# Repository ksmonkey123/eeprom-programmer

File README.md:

EEPROM Programmer
=================

Arduino-based EEPROM programmer for the AT28C64B (8 KiB) and AT28C256 (32 KiB) EEPROMs.

## Design

The EEPROM programmer consists of 2 parts:
A _Programmer Device_ based consiting of an Arduino Mega 2560 with a daughter-board containing an IC socket for the
EEPROM chips (DIP-28P6).
This _Programmer Device_ interacts with a _Client Program_ on the PC.

## Features

### Software Data Protection

The programmer supports enabling and disabling of the _Software Data Protection_ (Write Lockout) mode on the EEPROM.
This feature can be used as a standalone command (`<cmd> lock` and `<cmd> unlock`), and in combination with other _write
operations_.
It is even possible to unlock an EEPROM, write to it, and lock it again in a single operation.

### Automatic EEPROM size determination

Since the programmer supports 2 different sizes of EEPROMs, the user would have to indicate what type is connected to
the programmer for any given command.
The _Client Program_ is, however, capable of "guessing" the safe EEPROM size for most operations.
In some cases this may lead to additional unnecessary write cycles on smaller chips (which we consider to be a
negligible downside) and potentially increased operation durations.

The following pseudo-C shows the test routine to definitely determine the EEPROM size.
This test can be performed both destructively and non-desctructively.
In all cases the EEPROM _must_ be unlocked beforehand.

```c
bool isLargeChip(bool preserveData) {
  address adr = random(0x0000, 0x2000);
  byte data = read(adr);

  // if there's different data in the higher "blocks", it obviously is a large chip
  if (data != read(adr + 0x2000)) {
    return true;
  }

  // modify low byte, check if high byte changes too
  write(adr, ~data);
  //high byte unchanged means large chip
  bool result = (data == read(adr + 0x2000));

  if (preserveData) {
    write(adr, data);
  }
  return result;
}
```

### Considerate Writes

Unnecessary Write operations are avoided whenever possible. 
This means that the programmer will not write to a byte if the new value is the same as the old one.
This reduces both write times and wear on the EEPROM.

## Operations

### Erase

The `erase` opration writes `0xFF` to every byte of the EEPROM memory.
When an explicit size flag is set, the corresponding deletion logic is performed.
Otherwise, we perform a destructive _size test_ before flashing the EEPROM.

### Dump

The `dump` command reads the entire contents of the EEPROM.
If a size is specified, the output file has the matching size.
If no size is specified, the EEPROM is read as if it were a 32 KiB one.
After that the data is checked.
If all 4 8 KiB blocks match _exactly_, we assume to have read an 8 KiB EEPROM and write the output file with the
matching size.
If there are any differences in the blocks, we save the entire 32 KiB.

### Flash

The `flash` command writes a binary file to the EEPROM.

In cases where no chip size is provided, we perform a _size test_ before flashing the EEPROM.
It is always possible to write a binary file to the EEPROM that is smaller than the capacity of the EEPROM.
In that case, the memory locations not defined by the file remain unchanged.

It is never possible to write a file to an EEPROM that does not have enough capacity.

### Unlock

While the EEPROMs can be unlocked during write operations (erase / flash), a dedicated `unlock` command is also
provided.
Size information is not required for this operation.

### Lock

While the EEPROMs can be locked during write operations (erase / flash), a dedicated `lock` command is also provided.
Size information is not required for this operation.

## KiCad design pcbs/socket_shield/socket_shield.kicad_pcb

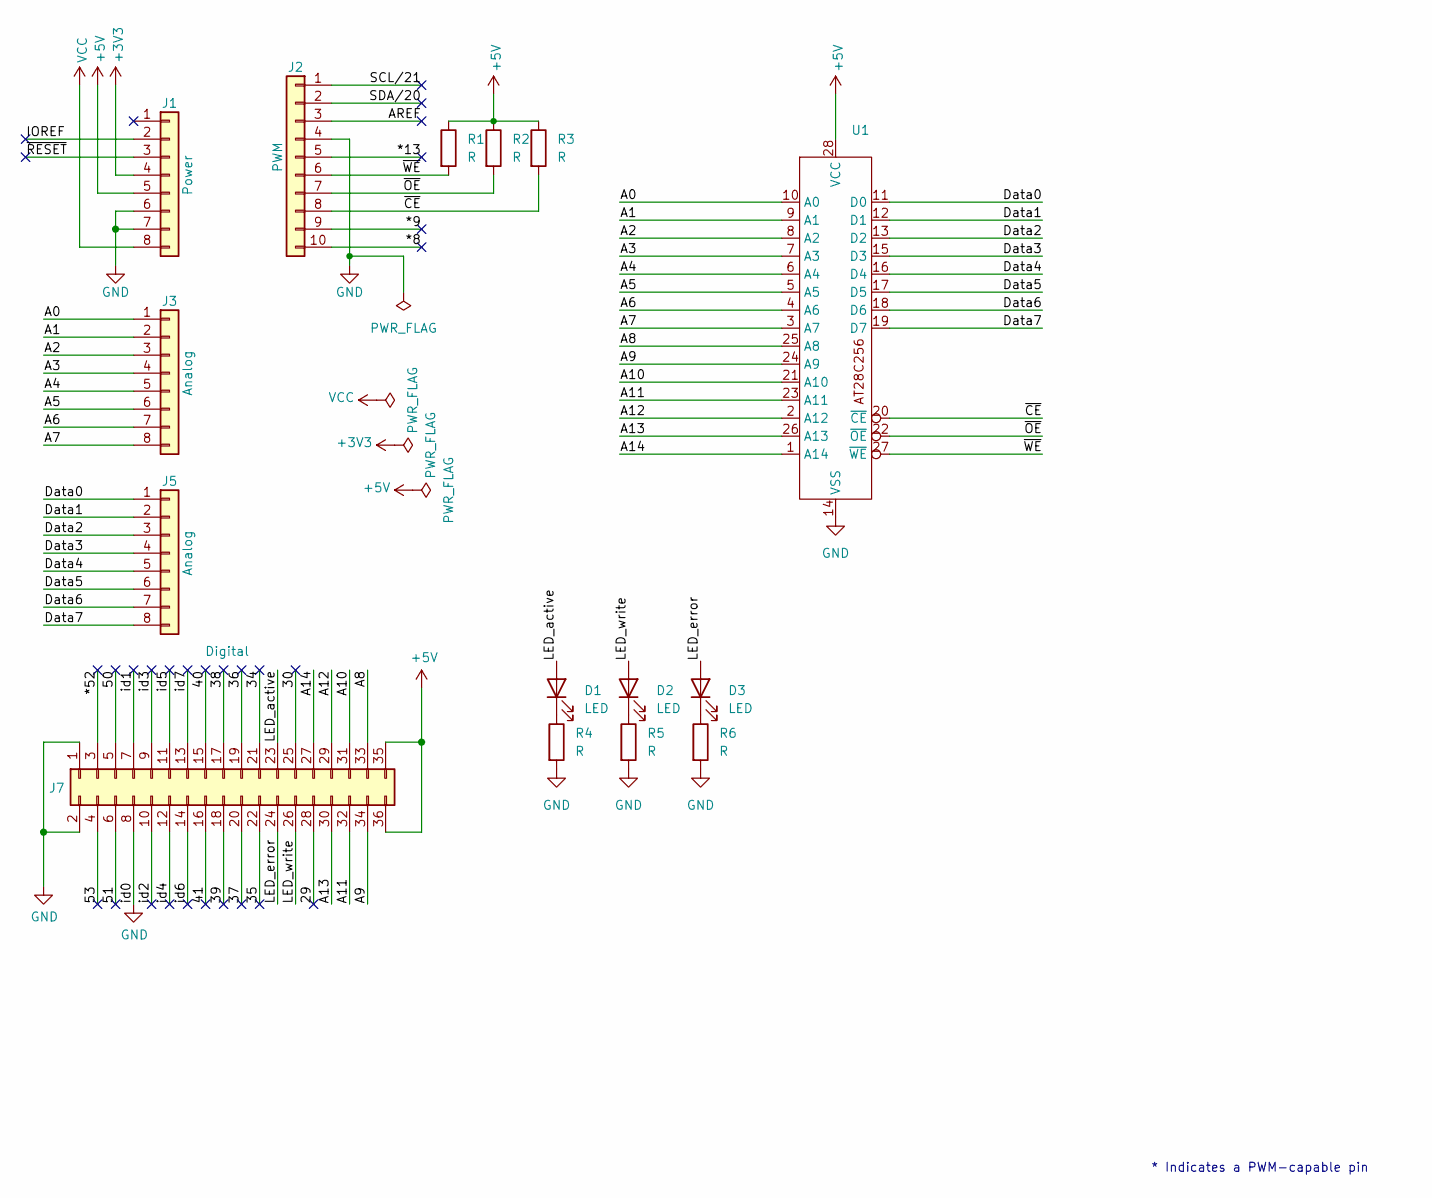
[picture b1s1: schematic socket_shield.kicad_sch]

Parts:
D1, D2, D3: LED; LED_0603_1608Metric
J1: Power; PinSocket_1x08_P2.54mm_Vertical
J2: PWM; PinSocket_1x10_P2.54mm_Vertical
J3, J5: Analog; PinSocket_1x08_P2.54mm_Vertical
J7: Digital; PinSocket_2x18_P2.54mm_Vertical
R1, R2, R3, R4, R5, R6: R; R_0603_1608Metric
U1: DIP-28_600_ELL

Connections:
+3V3: J1.4
+5V: J1.5, J7.35, J7.36, R1.1, R2.1, R3.1, U1.28 (VCC)
/29: J7.28
/30: J7.25
/34: J7.21
/35: J7.22
/36: J7.19
/37: J7.20
/38: J7.17
/39: J7.18
/40: J7.15
/41: J7.16
/50: J7.5
/51: J7.6
/53: J7.4
/*8: J2.10
/*9: J2.9
/*13: J2.5
/*52: J7.3
/A0: J3.1, U1.10 (A0)
/A1: J3.2, U1.9 (A1)
/A2: J3.3, U1.8 (A2)
/A3: J3.4, U1.7 (A3)
/A4: J3.5, U1.6 (A4)
/A5: J3.6, U1.5 (A5)
/A6: J3.7, U1.4 (A6)
/A7: J3.8, U1.3 (A7)
/A8: J7.33, U1.25 (A8)
/A9: J7.34, U1.24 (A9)
/A10: J7.31, U1.21 (A10)
/A11: J7.32, U1.23 (A11)
/A12: J7.29, U1.2 (A12)
/A13: J7.30, U1.26 (A13)
/A14: J7.27, U1.1 (A14)
/AREF: J2.3
/Data0: J5.1, U1.11 (D0)
/Data1: J5.2, U1.12 (D1)
/Data2: J5.3, U1.13 (D2)
/Data3: J5.4, U1.15 (D3)
/Data4: J5.5, U1.16 (D4)
/Data5: J5.6, U1.17 (D5)
/Data6: J5.7, U1.18 (D6)
/Data7: J5.8, U1.19 (D7)
/IOREF: J1.2
/LED_active: D1.2 (A), J7.23
/LED_error: D3.2 (A), J7.24
/LED_write: D2.2 (A), J7.26
/SCL/21: J2.1
/SDA/20: J2.2
/id1: J7.7
/id2: J7.10
/id3: J7.9
/id4: J7.12
/id5: J7.11
/id6: J7.14
/id7: J7.13
/~CE: J2.8, R3.2, U1.20 (~CE)
/~OE: J2.7, R2.2, U1.22 (~OE)
/~RESET: J1.3
/~WE: J2.6, R1.2, U1.27 (~WE)
GND: J1.6, J1.7, J2.4, J7.1, J7.2, J7.8, R4.2, R5.2, R6.2, U1.14 (VSS)
unnamed: D1.1 (K), R4.1
unnamed: D2.1 (K), R5.1
unnamed: D3.1 (K), R6.1
VCC: J1.8

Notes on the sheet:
* Indicates a PWM-capable pin

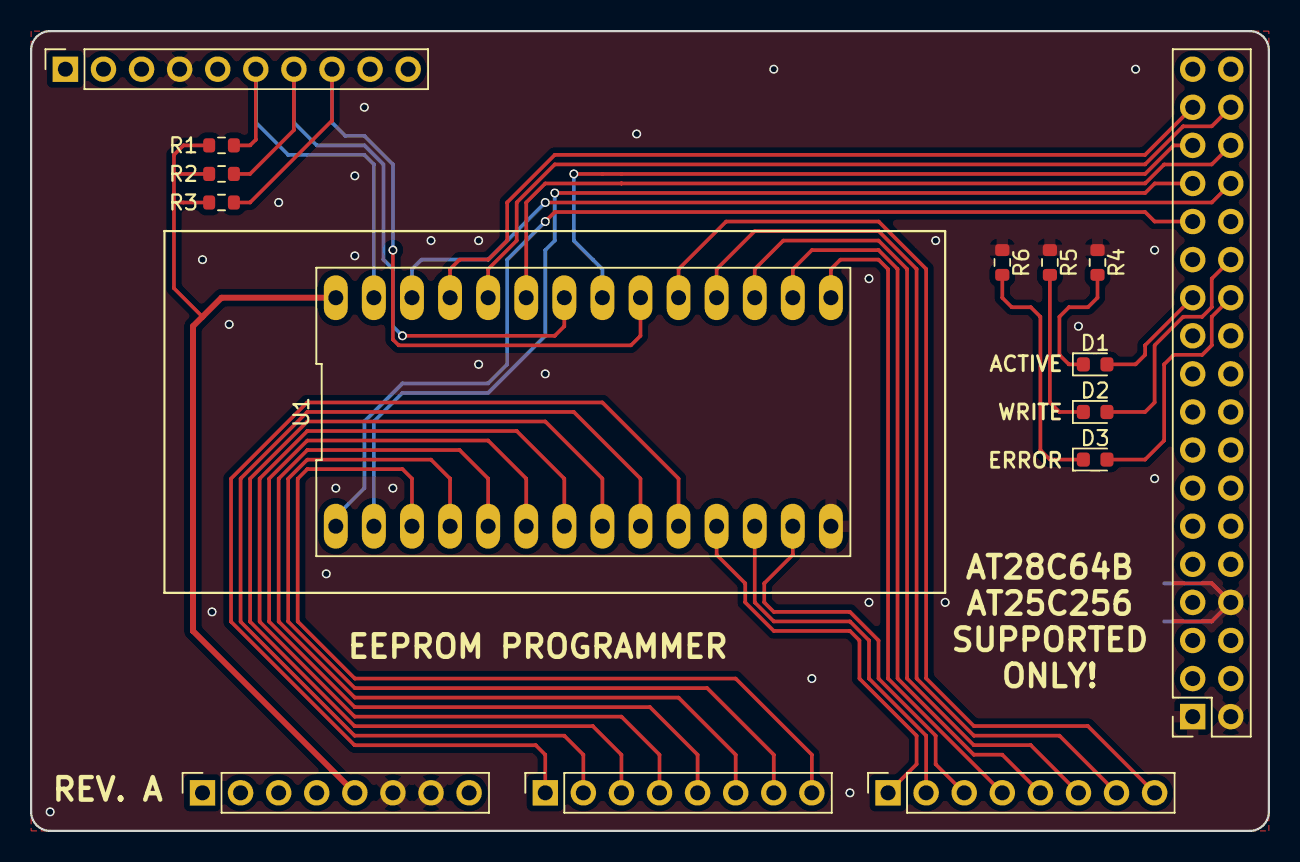
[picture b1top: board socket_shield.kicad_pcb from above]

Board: 2 copper layers, 82.6 x 53.3 mm, 15 parts (0 on the bottom side), 34 nets.

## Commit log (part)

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2025-01-13 initial implementation
2025-02-17 update firmware
    page commands were still missing in the committed version...
2025-11-04 Update Firmware to support AT28C256 too
2025-11-04 arduino shield PCB
2025-11-06 lock / unlock support. start rewrite
2025-11-07 continue
2025-11-07 add gitignore for pcb projects
2025-11-07 root directory for all pcbs. there will be more than just the socket shield, so it makes sense to bundle them.
2025-11-07 first working version of new firmware
2025-11-07 fix bad write error message in page write
2025-11-07 F-strings everywhere
2025-11-07 improvements in code readibility
2025-11-07 add lock / unlock commands
2025-11-07 drop old firmware
2025-11-07 drop old unused file
2025-11-10 firmware tweaks
2025-11-10 extended firmware with size test operation
2025-11-11 changed "size test" to "type identification"
2025-11-11 fix broken page write data parsing
2025-11-11 continued CLI
2025-11-11 start picocli implementation
2025-11-11 restructured to multi-module repo
2025-11-11 version bump to 2.0.x
2025-11-11 fix error in partial flashing
2025-11-12 add programmer support for sparse page writes: a sparse page write allows for select bytes in a page to be changed while not touching the rest of the page.
2025-11-12 firmware code cleanup
2025-11-12 reduce read delay from 100 to 10 microseconds. This improves read performance.
2025-11-18 change from raw binary files to hex files
2025-11-18 add option to erase chip on write
2025-11-21 increase hole sizes for socket
2025-11-21 add id pins at designate the socket shield as id 0x01
2025-11-27 upgrade binfiles to 0.2.0
2025-12-01 cleanup
